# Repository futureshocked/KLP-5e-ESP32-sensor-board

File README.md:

View this project on [CADLAB.io](https://cadlab.io/project/28685). 

## Project Summary: Custom IoT PCB with ESP32-C3-02 and TP4056 Li-ion Charger

This project involves the design and development of a custom PCB for an IoT application powered by the ESP32-C3-02 SoC. The board includes integrated power management features using the TP4056 Li-ion battery charger IC, enabling efficient and safe charging of a single-cell Li-ion battery.

### Key Features

- **Microcontroller**: ESP32-C3-02 SoC for Wi-Fi and BLE connectivity.
- **Power Management**: TP4056 IC for single-cell Li-ion battery charging with thermal regulation.
- **Battery Protection**: Integrated under-voltage lockout and trickle charging.
- **Sensors and Modules**:
  - BME280 for temperature, humidity, and pressure sensing.
  - Ambient light and sound sensors.
  - Mini SD card reader for data storage.
  - Flash memory for additional storage.
- **Display**: I2C OLED for real-time data visualization.
- **Power Inputs**:
  - USB-C connector for charging and data transfer.
  - LiPo battery connector with onboard charging circuitry.
- **Indicators**: LED indicators for charge status (charging and full).

### Design Highlights

1. **Power Supply Integration**:
   - USB-C provides power for both charging and system operation.
   - TP4056 handles battery charging and protection.
   - Power supplied to the ESP32-C3-02 is regulated for stability.

2. **Modular Architecture**:
   - Supports various sensors and peripherals for IoT applications.
   - Expandable via additional I2C devices.

3. **Safe and Efficient Charging**:
   - Programmable charging current using an external resistor.
   - Automatic charge termination and battery protection.

4. **Compact and Reliable Layout**:
   - Optimized PCB traces for minimal power loss.
   - Thermal management for the TP4056 and other components.

### Applications

- IoT edge devices for environmental monitoring.
- Battery-powered data logging systems.
- Prototyping platform for ESP32-based projects.

### Repository Contents

- **Schematic and PCB Layout**: KiCad files for the board design.
- **Firmware**: Source code for the ESP32-C3-02 to interface with sensors and peripherals.
- **Documentation**:
  - Datasheets for the TP4056 and other components.
  - Assembly instructions.
  - Testing procedures.
- **License**: MIT License.

This repository is a complete resource for designing and building a robust IoT solution with integrated power management and ESP32 connectivity.

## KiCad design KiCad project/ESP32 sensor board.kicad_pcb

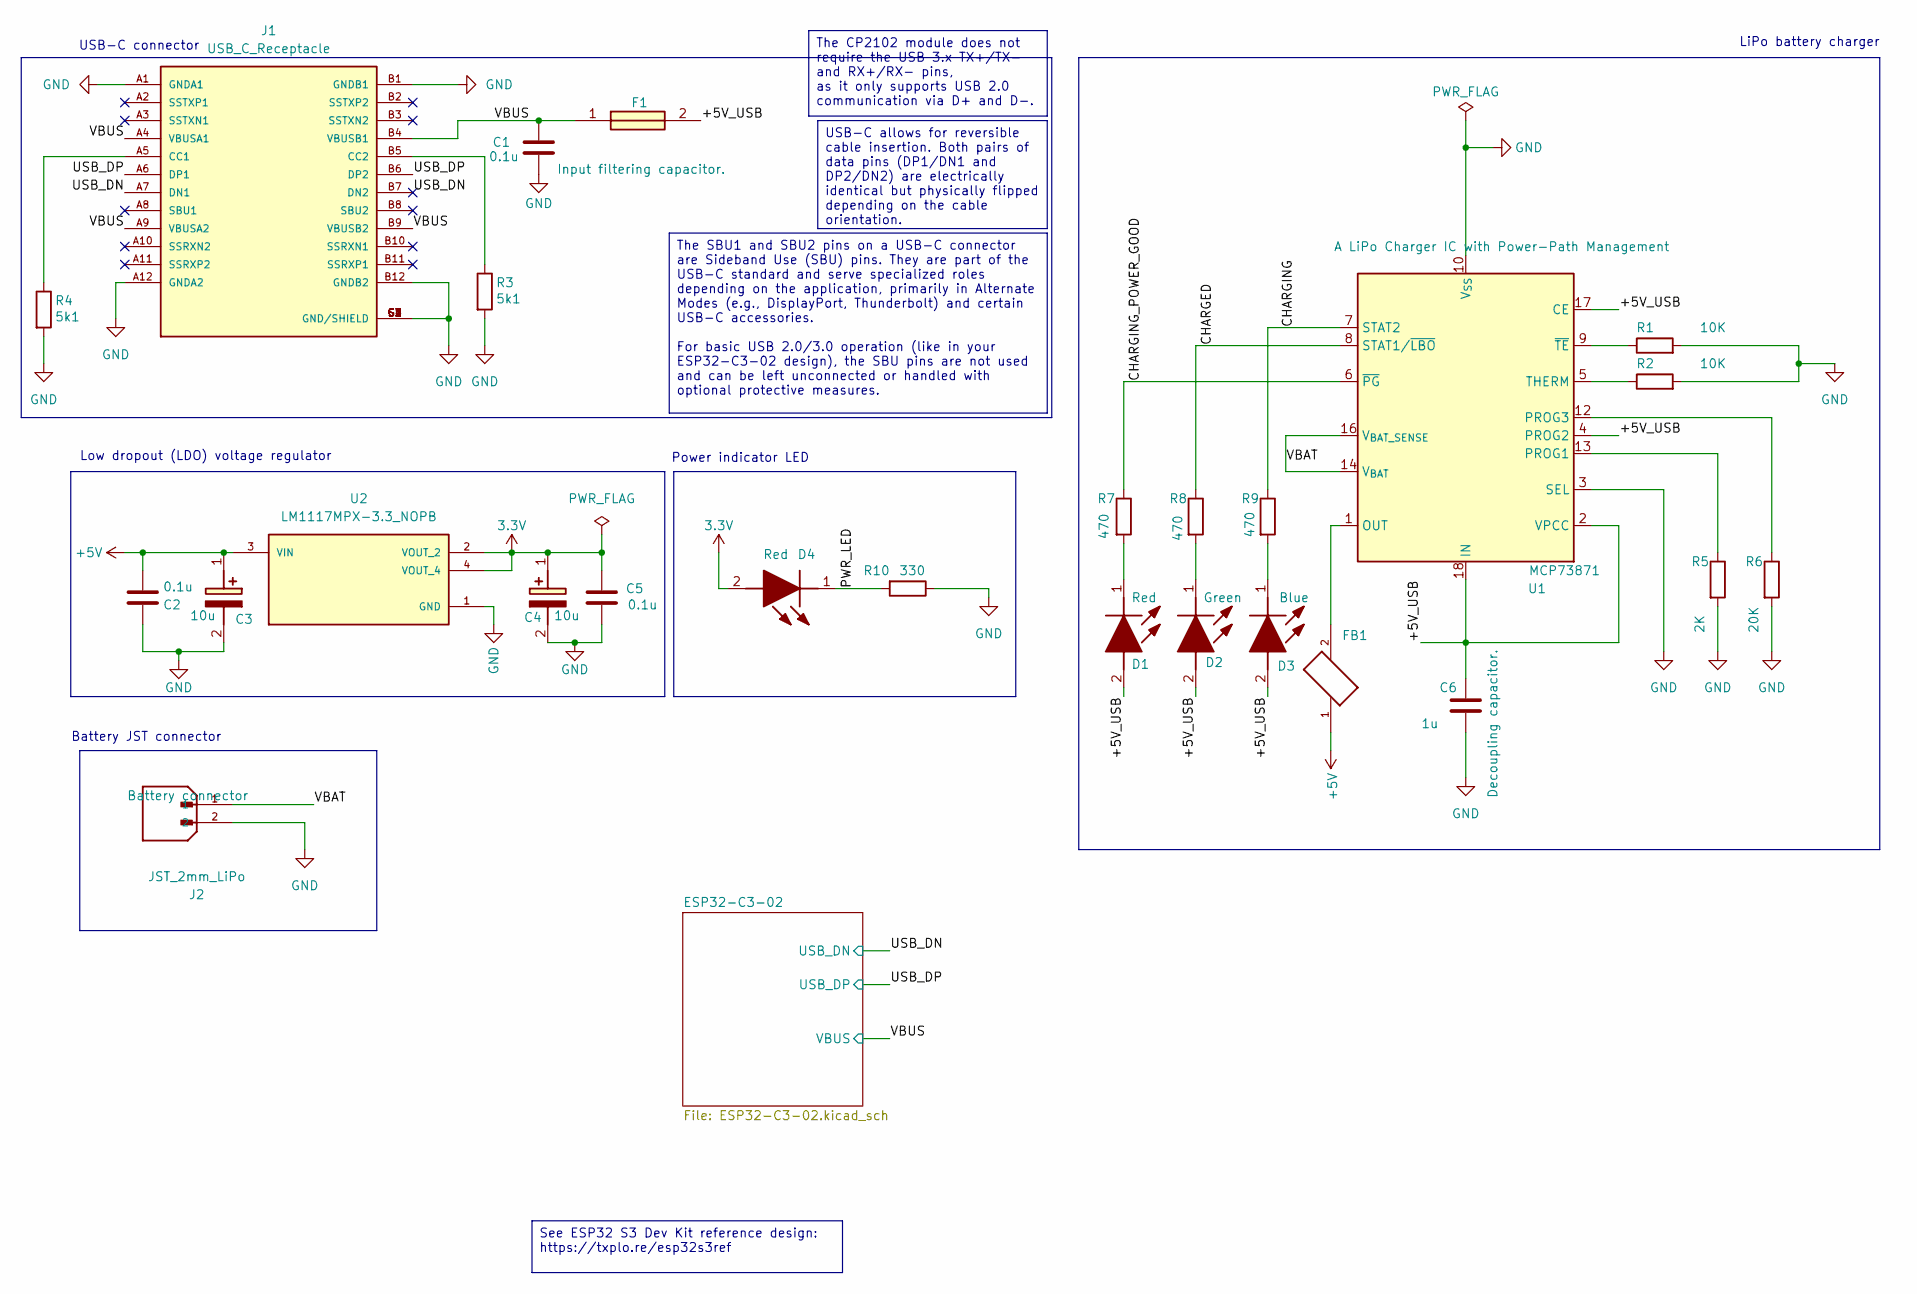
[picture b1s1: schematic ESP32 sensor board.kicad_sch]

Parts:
C1, C2, C5: 0.1u; C_0805_2012Metric; Voltage 1kV; Tolerance 100%
C3, C4: 10u; T491A; Voltage 1kV; Tolerance 100%; Manufacturer_Part_Number T491A106K010AT7280; Mouser Part Number 80-T491A106K107280
C6: 1u; C_0805_2012Metric; Voltage 1kV; Tolerance 100%
D1, D4: Red; LEDC2012X120N; Manufacturer_Part_Number LTST-C170KRKT; Mouser Part Number 859-LTST-C170KRKT
D2: Green; LEDC2012X120N; Manufacturer_Part_Number LTST-C170GKT; Mouser Part Number 859-LTST-C170GKT
D3: Blue; LEDC2012X120N; Manufacturer_Part_Number LTST-C170TBKT; Mouser Part Number 859-LTST-C170TBKT
F1: 0ZCH0110AF2E; FUSC3226X100N; Manufacturer_Part_Number 0ZCH0110AF2E
FB1: FBMJ2125HM330-T; BEADC2012X105N
J1: USB_C_Receptacle; BELFUSE_SS-52400-002; PARTREV A0
J2: JST_2mm_LiPo; JST_B2B-PH-SM4-TB; Manufacturer_Part_Number ?
R1, R2: 10K; R_0805_2012Metric
R3, R4: 5k1; R_0805_2012Metric
R5: 2K; R_0805_2012Metric
R6: 20K; R_0805_2012Metric
R7, R8, R9: 470; R_0805_2012Metric
R10: 330; R_0805_2012Metric
U1: MCP73871; QFN-20-1EP_4x4mm_P0.5mm_EP2.5x2.5mm; Manufacturer_Part_Number MCP73871-4CCI/ML
U2: LM1117MPX-3.3_NOPB; VREG_LM1117MPX-3.3; Mouser Part Number 926-LM1117MPX3.3NOPB

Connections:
3.3V: C4.1 (+), C5.1, D4.2 (A), U2.2 (VOUT_2), U2.4 (VOUT_4); also elsewhere on the board
+5V: C2.1, C3.1 (+), FB1.1, U2.3 (VIN)
/+5V_USB: C6.1, D1.2 (A), D2.2 (A), D3.2 (A), F1.2, U1.2 (VPCC), U1.4 (PROG2), U1.17 (CE), U1.18 (IN), U1.19 (IN)
/CHARGED: R8.1, U1.8 (STAT1/~LBO)
/CHARGING: R9.1, U1.7 (STAT2)
/CHARGING_POWER_GOOD: R7.1, U1.6 (~PG)
/PWR_LED: D4.1 (K), R10.2
/USB_DN: J1.A7 (DN1), J1.B7 (DN2); also elsewhere on the board
/USB_DP: J1.A6 (DP1), J1.B6 (DP2); also elsewhere on the board
/VBAT: J2.1, U1.14 (V_{BAT}), U1.15 (V_{BAT}), U1.16 (V_{BAT_SENSE})
/VBUS: C1.1, F1.1, J1.A4 (VBUSA1), J1.A9 (VBUSA2), J1.B4 (VBUSB1), J1.B9 (VBUSB2); also elsewhere on the board
GND: C1.2, C2.2, C3.2 (-), C4.2 (-), C5.2, C6.2, J1.A1 (GNDA1), J1.A12 (GNDA2), J1.B1 (GNDB1), J1.B12 (GNDB2), J1.G1 (GND/SHIELD), J1.G2 (GND/SHIELD), J1.G3 (GND/SHIELD), J1.G4 (GND/SHIELD), J1.S1 (GND/SHIELD), J1.S2 (GND/SHIELD), J1.S3 (GND/SHIELD), J1.S4 (GND/SHIELD), J2.2, R1.2, R2.2, R3.2, R4.2, R5.2, R6.2, R10.1, U1.3 (SEL), U1.10 (V_{SS}), U1.11 (V_{SS}), U1.21 (V_{SS}), U2.1 (GND); also elsewhere on the board
unnamed: D1.1 (K), R7.2
unnamed: D2.1 (K), R8.2
unnamed: D3.1 (K), R9.2
unnamed: FB1.2, U1.1 (OUT), U1.20 (OUT)
unnamed: J1.A5 (CC1), R4.1
unnamed: J1.B5 (CC2), R3.1
unnamed: R5.1, U1.13 (PROG1)
unnamed: R6.1, U1.12 (PROG3)
unnamed: R2.1, U1.5 (THERM)
unnamed: R1.1, U1.9 (~TE)

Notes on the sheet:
USB-C connector
LiPo battery charger
Power indicator LED
Low dropout (LDO) voltage regulator
Battery JST connector
The CP2102 module does not require the USB 3.x TX+/TX- and RX+/RX- pins, as it only supports USB 2.0 communication via D+ and D-.
See ESP32 S3 Dev Kit reference design: https://txplo.re/esp32s3ref
The SBU1 and SBU2 pins on a USB-C connector are Sideband Use (SBU) pins. They are part of the USB-C standard and serve specialized roles depending on the application, primarily in Alternate Modes (e.g., DisplayPort, Thunderbolt) and certain USB-C accessories. For basic USB 2.0/3.0 operation (like i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
USB-C allows for reversible cable insertion. Both pairs of data pins (DP1/DN1 and DP2/DN2) are electrically identical but physically flipped depending on the cable orientation.

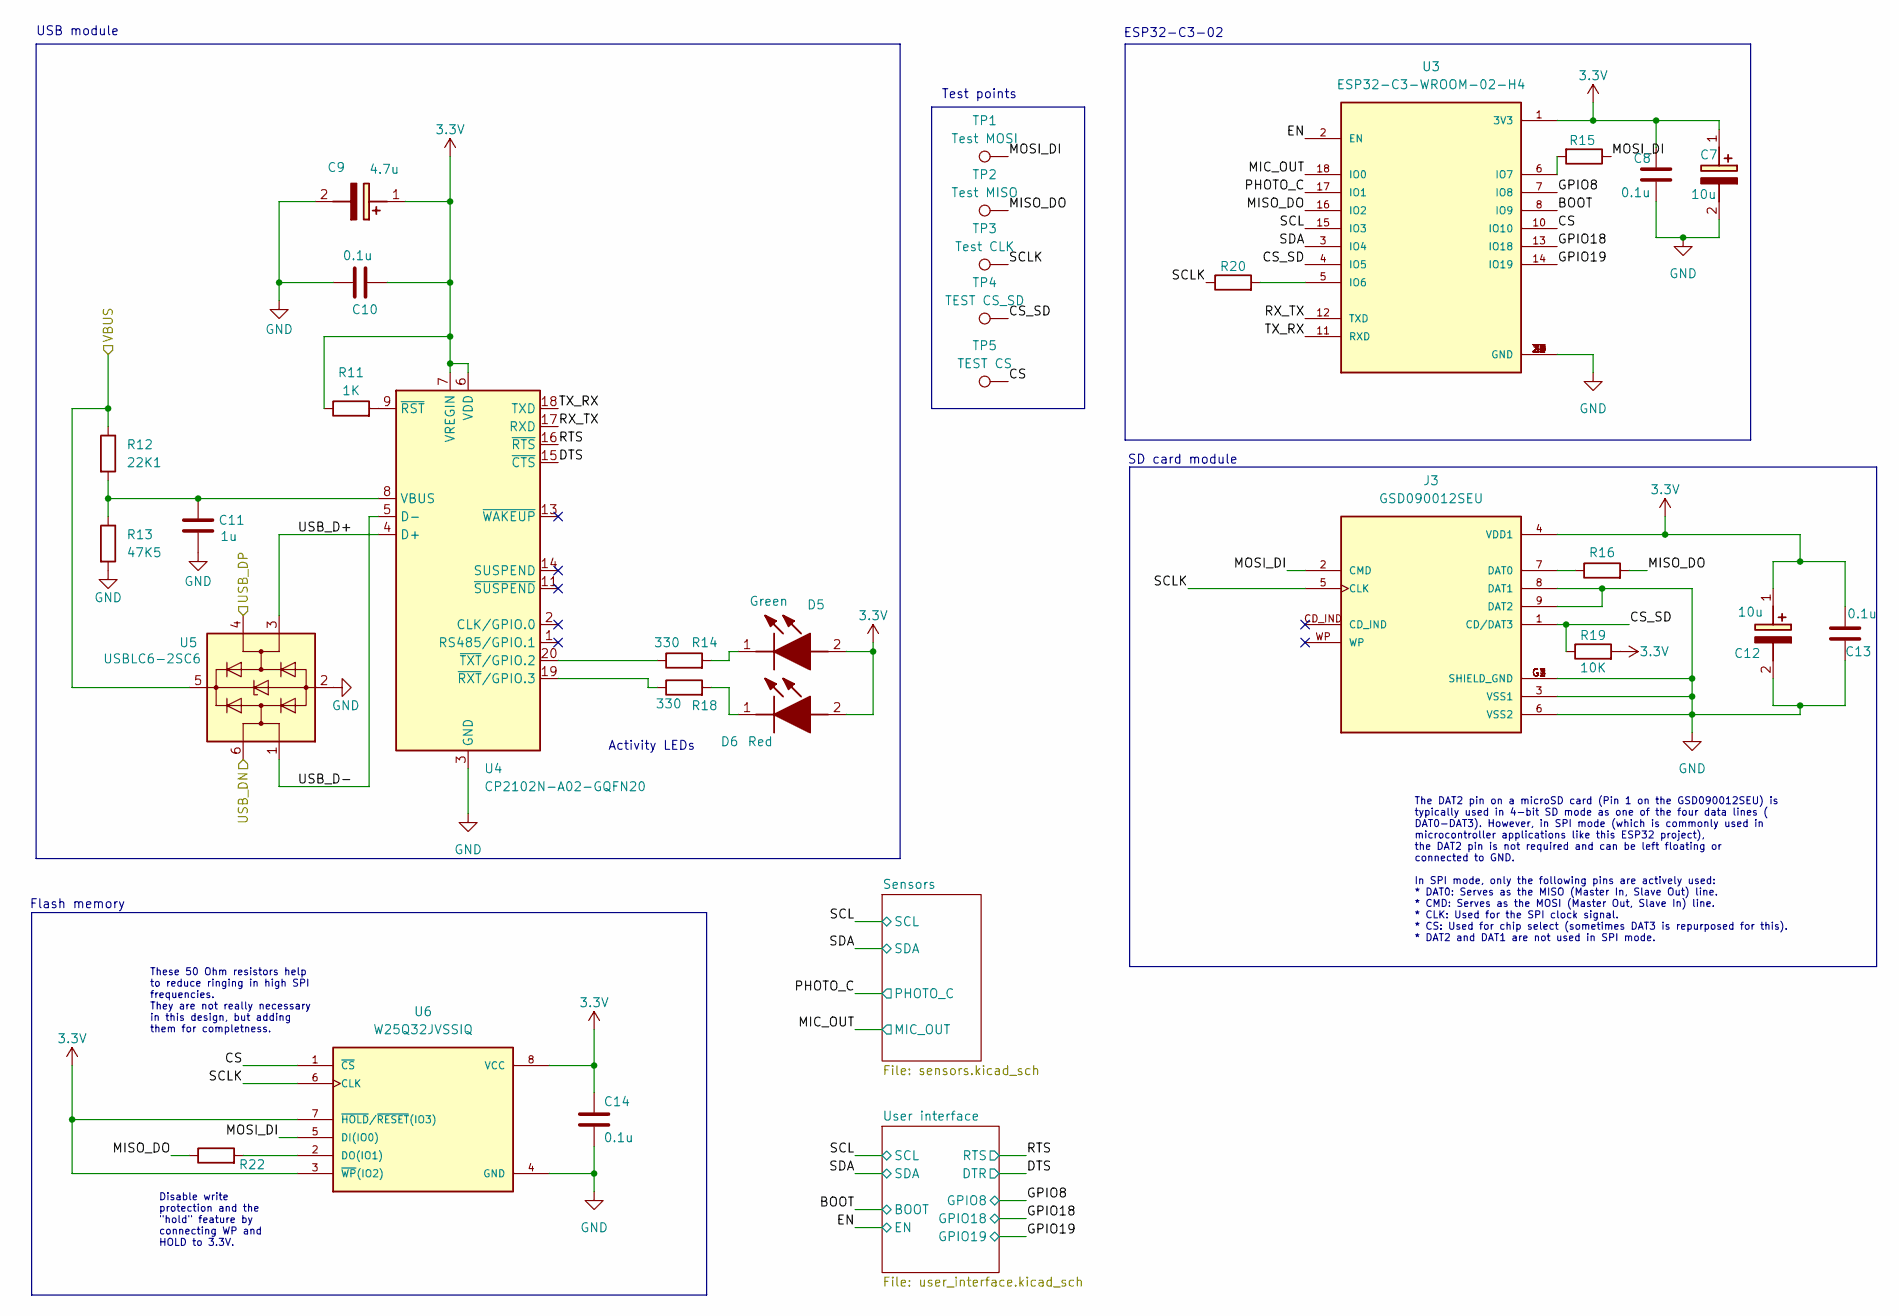
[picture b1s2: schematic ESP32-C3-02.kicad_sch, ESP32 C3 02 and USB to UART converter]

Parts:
C7, C12: 10u; T491A; Voltage 1kV; Tolerance 100%; Manufacturer_Part_Number T491A106K010AT7280; Mouser Part Number 80-T491A106K107280
C8, C10, C13, C14: 0.1u; C_0805_2012Metric; Voltage 1kV; Tolerance 100%
C9: 4.7u; T491A; Voltage 1kV; Tolerance 100%; Manufacturer_Part_Number T491A106K010AT7280; Mouser Part Number 80-T491A106K107280
C11: 1u; C_0805_2012Metric; Voltage 1kV; Tolerance 100%
D5: Green; LEDC2012X120N; Manufacturer_Part_Number LTST-C170GKT; Mouser Part Number 859-LTST-C170GKT
D6: Red; LEDC2012X120N; Manufacturer_Part_Number LTST-C170KRKT; Mouser Part Number 859-LTST-C170KRKT
J3: GSD090012SEU; AMPHENOL_GSD090012SEU; PARTREV E
R11: 1K; R_0805_2012Metric
R12: 22K1; R_0805_2012Metric
R13: 47K5; R_0805_2012Metric
R14, R18: 330; R_0805_2012Metric
R15, R16, R20, R22: 50; R_0805_2012Metric
R19: 10K; R_0805_2012Metric
TP1: Test MOSI; TestPoint_Pad_D1.0mm
TP2: Test MISO; TestPoint_Pad_D1.0mm
TP3: Test CLK; TestPoint_Pad_D1.0mm
TP4: TEST CS_SD; TestPoint_Pad_D1.0mm
TP5: TEST CS; TestPoint_Pad_D1.0mm
U3: ESP32-C3-WROOM-02-H4; MODULE_ESP32-C3-WROOM-02-H4; Manufacturer_Part_Number ESP32-C3-WROOM-02-H4
U4: CP2102N-A02-GQFN20; SiliconLabs_QFN-20-1EP_3x3mm_P0.5mm_EP1.8x1.8mm; Manufacturer_Part_Number CP2102N-A02-GQFN20
U5: USBLC6-2SC6; SOT-23-6; Manufacturer_Part_Number USBLC6-2SC6; Mouser Part Number 511-USBLC6-2SC6
U6: W25Q32JVSSIQ; SOIC127P790X216-8N; M_PART_NUMBER W25QXX

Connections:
3.3V: C7.1 (+), C8.1, C9.1 (+), C10.1, C12.1 (+), C13.2, C14.1, D5.2 (A), D6.2 (A), J3.4 (VDD1), R11.1, R19.2, U3.1 (3V3), U4.6 (VDD), U4.7 (VREGIN), U6.3 (~WP(IO2)), U6.7 (~HOLD/~RESET(IO3)), U6.8 (VCC); also elsewhere on the board
/ESP32-C3-02/BOOT: U3.8 (IO9); also elsewhere on the board
/ESP32-C3-02/CS: TP5.1, U3.10 (IO10), U6.1 (~CS)
/ESP32-C3-02/CS_SD: J3.1 (CD/DAT3), R19.1, TP4.1, U3.4 (IO5)
/ESP32-C3-02/DTS: U4.15 (~CTS); also elsewhere on the board
/ESP32-C3-02/EN: U3.2 (EN); also elsewhere on the board
/ESP32-C3-02/GPIO8: U3.7 (IO8); also elsewhere on the board
/ESP32-C3-02/GPIO18: U3.13 (IO18); also elsewhere on the board
/ESP32-C3-02/GPIO19: U3.14 (IO19); also elsewhere on the board
/ESP32-C3-02/MIC_OUT: U3.18 (IO0); also elsewhere on the board
/ESP32-C3-02/MISO_DO: R16.2, R22.1, TP2.1, U3.16 (IO2)
/ESP32-C3-02/MOSI_DI: J3.2 (CMD), R15.1, TP1.1, U6.5 (DI(IO0))
/ESP32-C3-02/PHOTO_C: U3.17 (IO1); also elsewhere on the board
/ESP32-C3-02/RTS: U4.16 (~RTS); also elsewhere on the board
/ESP32-C3-02/RX_TX: U3.12 (TXD), U4.17 (RXD)
/ESP32-C3-02/SCL: U3.15 (IO3); also elsewhere on the board
/ESP32-C3-02/SCLK: J3.5 (CLK), R20.1, TP3.1, U6.6 (CLK)
/ESP32-C3-02/SDA: U3.3 (IO4); also elsewhere on the board
/ESP32-C3-02/TX_RX: U3.11 (RXD), U4.18 (TXD)
/ESP32-C3-02/USB_D+: U4.4 (D+), U5.3 (I/O2)
/ESP32-C3-02/USB_D-: U4.5 (D-), U5.1 (I/O1)
/USB_DN: U5.6 (I/O1); also elsewhere on the board
/USB_DP: U5.4 (I/O2); also elsewhere on the board
/VBUS: R12.1, U5.5 (VBUS); also elsewhere on the board
GND: C7.2 (-), C8.2, C9.2 (-), C10.2, C11.2, C12.2 (-), C13.1, C14.2, J3.3 (VSS1), J3.6 (VSS2), J3.8 (DAT1), J3.9 (DAT2), J3.G1 (SHIELD_GND), J3.G2 (SHIELD_GND), J3.G3 (SHIELD_GND), J3.G4 (SHIELD_GND), R13.2, U3.9 (GND), U3.19 (GND), U3.20 (GND), U3.21 (GND), U3.22 (GND), U3.23 (GND), U3.24 (GND), U3.25 (GND), U3.26 (GND), U3.27 (GND), U3.28 (GND), U3.29 (GND), U3.30 (GND), U3.31 (GND), U3.32 (GND), U3.33 (GND), U3.34 (GND), U3.35 (GND), U3.36 (GND), U3.37 (GND), U3.38 (GND), U3.39 (GND), U4.3 (GND), U4.12 (GND), U4.21 (GND), U5.2 (GND), U6.4 (GND); also elsewhere on the board
unnamed: D5.1 (K), R14.2
unnamed: D6.1 (K), R18.2
unnamed: J3.7 (DAT0), R16.1
unnamed: R20.2, U3.5 (IO6)
unnamed: R15.2, U3.6 (IO7)
unnamed: C11.1, R12.2, R13.1, U4.8 (VBUS)
unnamed: R11.2, U4.9 (~RST)
unnamed: R18.1, U4.19 (~RXT/GPIO.3)
unnamed: R14.1, U4.20 (~TXT/GPIO.2)
unnamed: R22.2, U6.2 (DO(IO1))

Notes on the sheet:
SD card module
Activity LEDs
Flash memory
USB module
Test points
ESP32-C3-02
Disable write protection and the "hold" feature by connecting WP and HOLD to 3.3V.
The DAT2 pin on a microSD card (Pin 1 on the GSD090012SEU) is typically used in 4-bit SD mode as one of the four data lines ( DAT0-DAT3). However, in SPI mode (which is commonly used in microcontroller applications like this ESP32 project), the DAT2 pin is not required and can be left floating or c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
These 50 Ohm resistors help to reduce ringing in high SPI frequencies. They are not really necessary in this design, but adding them for completness.

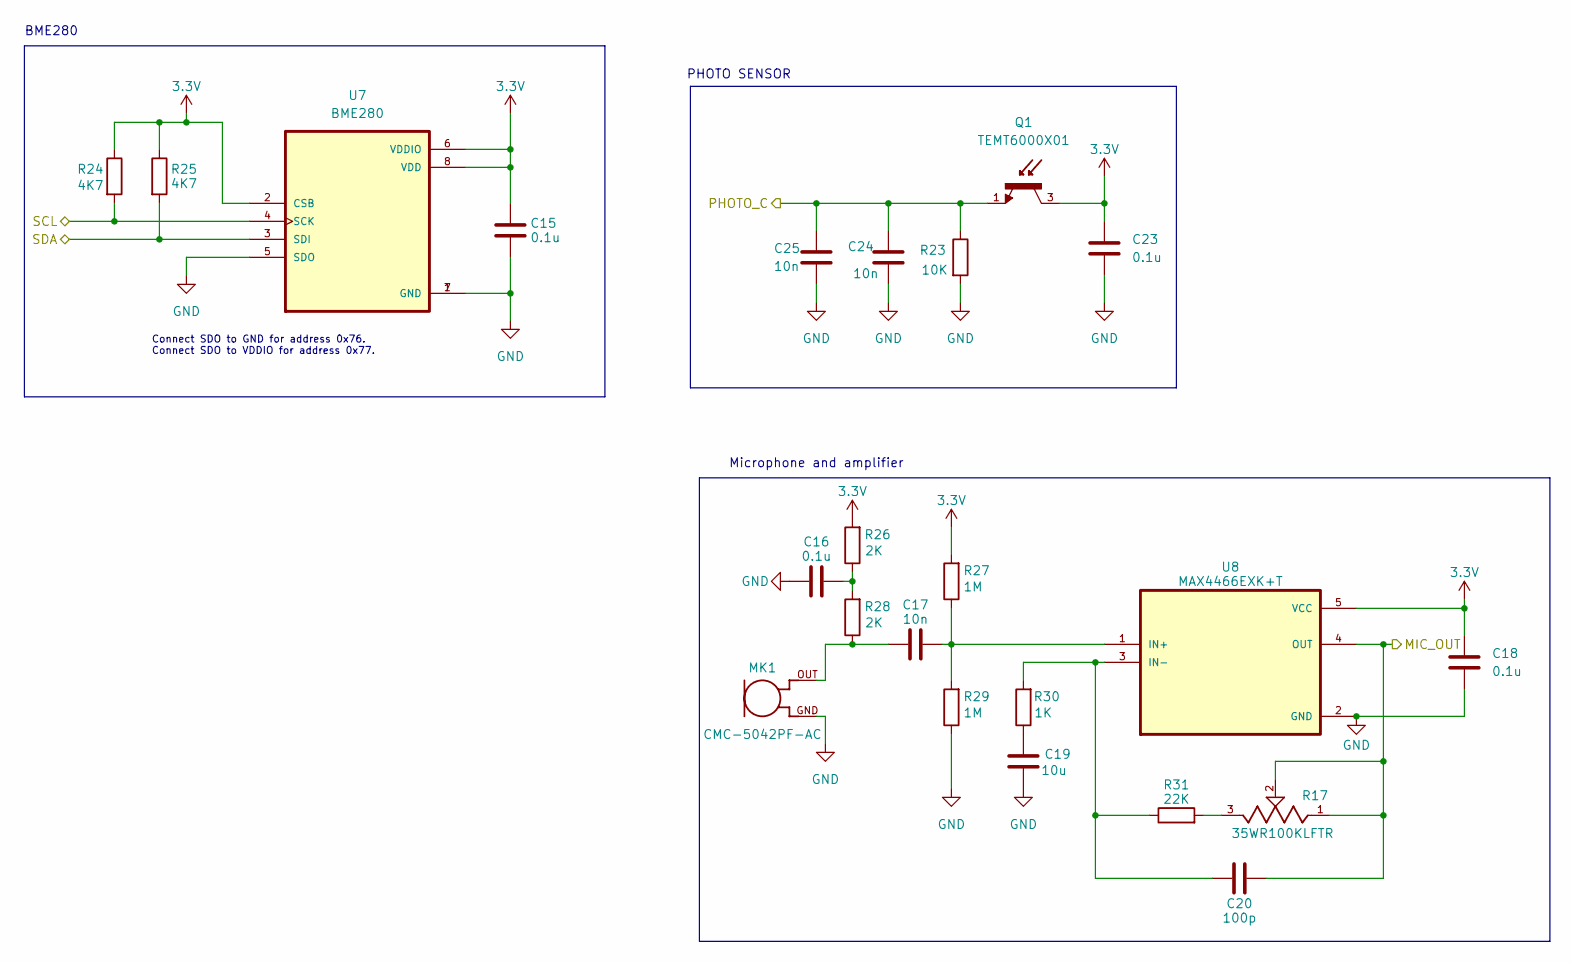
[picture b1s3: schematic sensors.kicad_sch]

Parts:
C15: 0.1u; C_0805_2012Metric; Voltage 1kV; Tolerance 100%
C16, C18, C23: 0.1u; C_0805_2012Metric
C17, C24, C25: 10n; C_0805_2012Metric
C19: 10u; C_0805_2012Metric
C20: 100p; C_0805_2012Metric
MK1: CMC-5042PF-AC; CUI_CMC-5042PF-AC; Manufacturer_Part_Number CMC-5042PF-AC
Q1: TEMT6000X01; TRANS_TEMT6000X01; PARTREV 1.9
R17: 35WR100KLFTR; TRIM_35WR100KLFTR; PARTREV D
R23: 10K; R_0805_2012Metric
R24, R25: 4K7; R_0805_2012Metric
R26, R28: 2K; R_0805_2012Metric
R27, R29: 1M; R_0805_2012Metric
R30: 1K; R_0805_2012Metric
R31: 22K; R_0805_2012Metric
U7: BME280; PSON65P250X250X100-8N; Manufacturer_Part_Number BME280
U8: MAX4466EXK+T; SOT65P210X110-5N; Manufacturer_Part_Number MAX4466EXK+T

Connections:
3.3V: C15.2, C18.1, C23.1, Q1.3, R24.1, R25.1, R26.2, R27.2, U7.2 (CSB), U7.6 (VDDIO), U7.8 (VDD), U8.5 (VCC); also elsewhere on the board
/ESP32-C3-02/MIC_OUT: C20.2, R17.1, R17.2, U8.4 (OUT); also elsewhere on the board
/ESP32-C3-02/PHOTO_C: C24.1, C25.1, Q1.1, R23.1; also elsewhere on the board
/ESP32-C3-02/SCL: R24.2, U7.4 (SCK); also elsewhere on the board
/ESP32-C3-02/SDA: R25.2, U7.3 (SDI); also elsewhere on the board
GND: C15.1, C16.2, C18.2, C19.1, C23.2, C24.2, C25.2, MK1.GND, R23.2, R29.1, U7.1 (GND), U7.5 (SDO), U7.7 (GND), U8.2 (GND); also elsewhere on the board
unnamed: C16.1, R26.1, R28.2
unnamed: C17.2, MK1.OUT, R28.1
unnamed: C19.2, R30.1
unnamed: R17.3, R31.2
unnamed: C17.1, R27.1, R29.2, U8.1 (IN+)
unnamed: C20.1, R30.2, R31.1, U8.3 (IN-)

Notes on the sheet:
PHOTO SENSOR
Microphone and amplifier
BME280
Connect SDO to GND for address 0x76. Connect SDO to VDDIO for address 0x77.

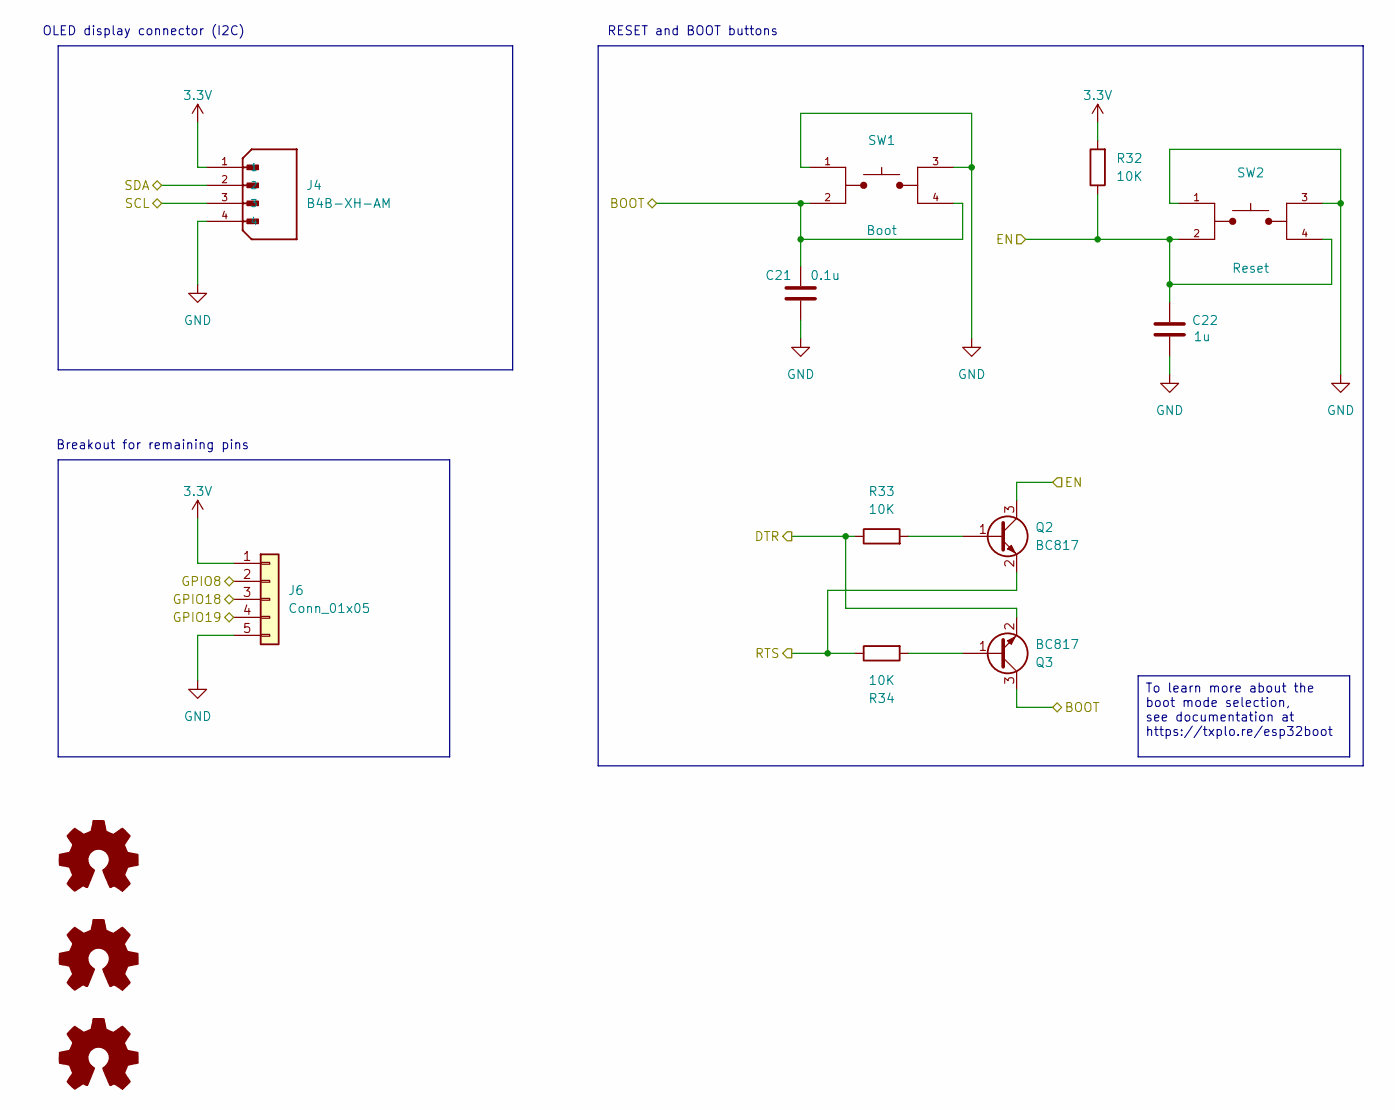
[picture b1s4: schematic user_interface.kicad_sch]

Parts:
C21: 0.1u; C_0805_2012Metric; Voltage 1kV; Tolerance 100%
C22: 1u; C_0805_2012Metric; Voltage 1kV; Tolerance 100%
J4: B4B-XH-AM; JST_B4B-XH-AM__LF__SN_; PARTREV N/A
J6: Conn_01x05; PinHeader_1x05_P2.54mm_Vertical
Q2, Q3: BC817; SOT-23; Manufacturer_Part_Number BC817
R32, R33, R34: 10K; R_0805_2012Metric
SW1, SW2: 1101NE; SW_TL3305AF260QG; Mfg Part# 8-004 SMD Button 8x3.6mm Height=2.5mm

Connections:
3.3V: J4.1, J6.1, R32.2; also elsewhere on the board
/ESP32-C3-02/BOOT: C21.1, Q3.3 (C), SW1.2, SW1.4; also elsewhere on the board
/ESP32-C3-02/DTS: Q3.2 (E), R33.1; also elsewhere on the board
/ESP32-C3-02/EN: C22.1, Q2.3 (C), R32.1, SW2.2, SW2.4; also elsewhere on the board
/ESP32-C3-02/GPIO8: J6.2; also elsewhere on the board
/ESP32-C3-02/GPIO18: J6.3; also elsewhere on the board
/ESP32-C3-02/GPIO19: J6.4; also elsewhere on the board
/ESP32-C3-02/RTS: Q2.2 (E), R34.1; also elsewhere on the board
/ESP32-C3-02/SCL: J4.3; also elsewhere on the board
/ESP32-C3-02/SDA: J4.2; also elsewhere on the board
GND: C21.2, C22.2, J4.4, J6.5, SW1.1, SW1.3, SW2.1, SW2.3; also elsewhere on the board
unnamed: Q2.1 (B), R33.2
unnamed: Q3.1 (B), R34.2

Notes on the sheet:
OLED display connector (I2C)
RESET and BOOT buttons
Breakout for remaining pins
To learn more about the boot mode selection, see documentation at https://txplo.re/esp32boot

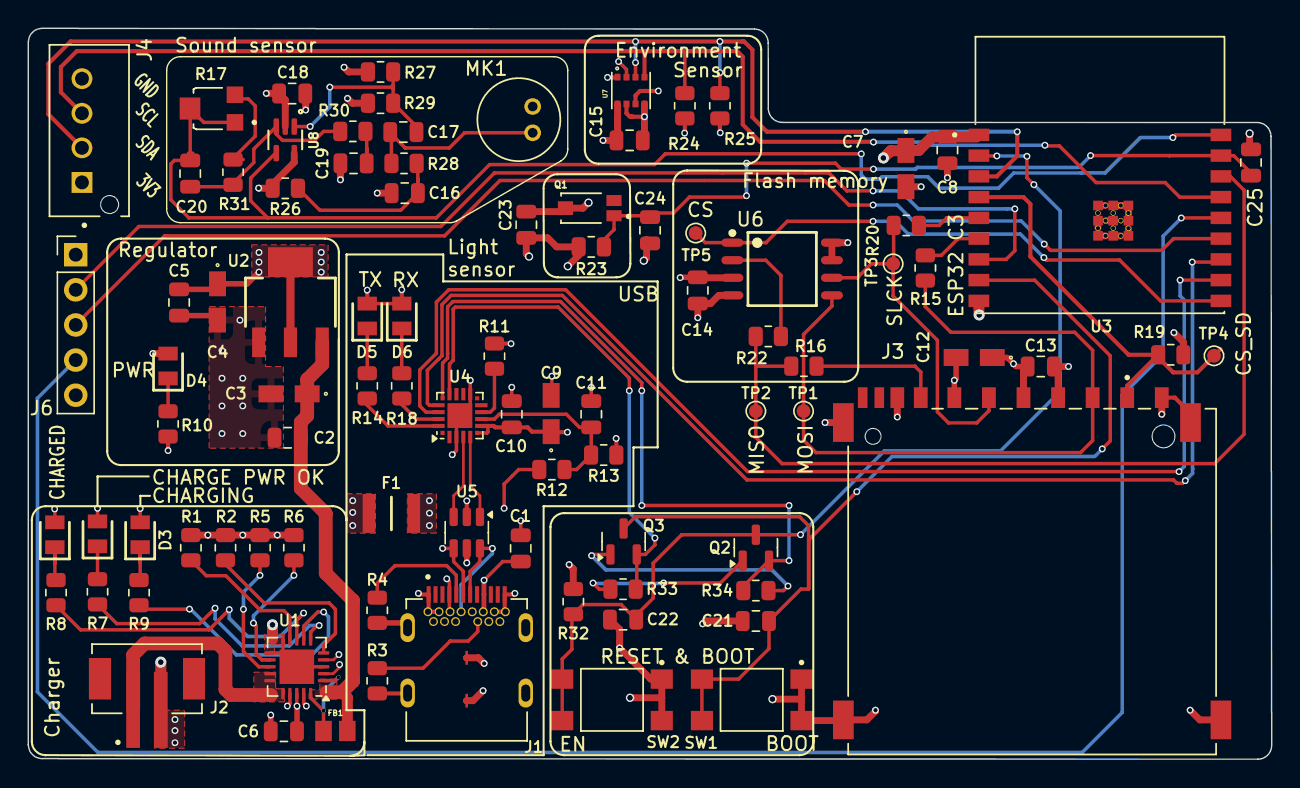
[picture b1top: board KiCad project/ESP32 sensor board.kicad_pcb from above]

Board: 4 copper layers, 89.9 x 52.8 mm, 90 parts (0 on the bottom side), 60 nets.

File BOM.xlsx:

DESIGNATOR | QTY | VALUE | MANUF. PART No | MANUFACTURER | PACKAGE | DESCRIPTION
> C1, C2, C5, C8, C10, C13-C16, C18, C20, C21 | 12 | 0.1u | C0805C104K4RAC | KEMET | 805 | Multilayer Ceramic Capacitors MLCC - SMD/SMT 16V 0.1uF X7R 0805 10%
> C3, C4, C7, C12 | 4 | 10u | T491A106K010AT7280 | KEMET | 1206 | T491, Tantalum, MnO2 Tantalum, Commercial Grade, 10 uF, 10%, 10 VDC, 125C, -55C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
> C6, C11, C19, C22 | 4 | 1u | C0805C105K4RACTU | KEMET | 805 | Multilayer Ceramic Capacitors MLCC - SMD/SMT 16V 1uF X7R 0805 10%
C9 | 1 | 4.7u | T491A475K010AT7280 | KEMET | 1206 | T491, Tantalum, MnO2 Tantalum, Commercial Grade, 4.7 uF, 10%, 10 VDC, 125C, -55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
C17 | 1 | 10n | C0805C103M4RACTU | KEMET | 805 | Multilayer Ceramic Capacitors MLCC - SMD/SMT 16V 0.01uF X7R 0805 20%
> D1, D4, D6 | 3 | RED | LTST-C170KRKT | Lite-On | 805 | Standard LEDs - SMD Red Clear 631nm
> D2, D5 | 2 | GREEN | LTST-C170GKT | Lite-On | 805 | LED,SMD,0805,Green,6mcd,130deg Lite-On LTST-C170GKT, CHIPLED 0805 Series Green 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
D3 | 1 | BLUE | LTST-C170TBKT | Lite-On | 805 | LED,SMD,0805,Blue,28mcd,130deg
F1 | 1 | 0ZCH0110AF2E | 0ZCH0110AF2E | Belfuse | 1210 | 1210 SMT PPTC | 1.10 Ih | 16V
J1 | 1 | USB_C_Receptacle | Footprints:BELFUSE_SS-52400-002 | BELFUSE Stewart Connector | SS-52400-003 for standard 1.6 mm PCB thickness | USB 2.0-only Type-C Receptacle connector. See https://www.snapeda.com/parts/SS-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
J2 | 1 | JST_2mm_LiPo | JST_B2B-PH-SM4-TB | JST |  | 2 Pin 2mm JST Battery Connector
J3 | 1 | GSD090012SEU | GSD090012SEU | Amphenol |  | Memory Card Connectors SD CARD CONNECTOR 9 POS, SMT
> J4, J5 | 2 | B4B-XH-AM | B4B-XH-AM | JST |  | Connector header vertical 4pos 2.5mm
J6 | 1 | Conn_01x05 |  |  |  | Header 1X5, 2.54mm
MK1 | 1 | CMC-5042PF-AC | CMC-5042PF-AC | CUI INC |  | Microphone
Q1 | 1 | TEMT6000X01 | TEMT6000X01 | VISHAY | 4 mm x 2 mm x 1.05 mm | Ambient Light Sensors Ambient Light Sensor AEC-Q101 Qualified
> Q2, Q3 | 2 | BC817 | BC817 |  | SOT-23 | 0.8A Ic, 45V Vce, NPN Transistor, SOT-23
> R1, R2, R19, R23, R30, R32-R34 | 8 | 10K |  |  | 805 | SMD resistor, 0805, 125mW, 1%
> R3, R4 | 2 | 5k1 |  |  | 0805 | SMD resistor, 0805, 125mW, 1%
> R5, R26, R28 | 3 | 2K |  |  | 0805 | SMD resistor, 0805, 125mW, 1%
R6 | 1 | 20K |  |  | 0805 | SMD resistor, 0805, 125mW, 1%
> R7-R9 | 3 | 470 |  |  | 0805 | SMD resistor, 0805, 125mW, 1%
> R10, R14, R18 | 3 | 330 |  |  | 0805 | SMD resistor, 0805, 125mW, 1%
R11 | 1 | 1K |  |  | 0805 | SMD resistor, 0805, 125mW, 1%
R12 | 1 | 22K1 |  |  | 0805 | SMD resistor, 0805, 125mW, 1%
R13 | 1 | 47K5 |  |  | 0805 | SMD resistor, 0805, 125mW, 1%
> R15-R17, R20-R22 | 6 | 50 |  |  | 0805 | SMD resistor, 0805, 125mW, 1%
> R24, R25 | 2 | 4K7 |  |  | 0805 | SMD resistor, 0805, 125mW, 1%
> R27, R29 | 2 | 1M |  |  | 0805 | SMD resistor, 0805, 125mW, 1%
R31 | 1 | 100K |  |  | 0805 | SMD resistor, 0805, 125mW, 1%
> SW1, SW2 | 2 | 1101NE | USLPT2819 Family | TE Connectivity | USLPT2819 MSLPT (Mini size) | SMD_6x3.5mm_h2.5mm. Please see https://www.snapeda.com/parts/USLPT2819DT2TR/TE%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
U1 | 1 | MCP73871 | MCP73871-4CCI/ML | Microchip | QFN50P400X400X100-21N | Single cell, Li-Ion/Li-Po charge management controller. See https://www.snapeda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
U2 | 1 | LM1117MPX-3.3_NOPB | LM1117MPX-33NOPB | On Semiconductor | SOT−223 CASE 318H | See https://www.snapeda.com/parts/LM1117MPX-33NOPB/ON%20Semicond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
U3 | 1 | ESP32-C3-WROOM-02-H4 | ESP32-C3-WROOM-02-H4 | Espressif |  | Multiprotocol Modules SMD module, ESP32-C3, 4MB SPI flash, PCB antenna
U4 | 1 | CP2102N-A02-GQFN20 | CP2102N-A02-GQFN20 | Silicon Laboratories | QFN20 | USB to UART Bridge
U5 | 1 | USBLC6-2SC6 | USBLC6-2SC6 | STMicroelectronics | SOT-23-6 | ESD Suppressors / TVS Diodes ESD Protection Low Cap
U6 | 1 | W25Q32JVSSIQ | W25Q32JVSSIQ | Winbond | SOIC-8 | NOR Flash spiFlash, 32M-bit, 4Kb Uniform Sector
U7 | 1 | BME280 | BME280 | Bosch | LGA-8 | Air Quality Sensor MEMS humidity, pressure and temperature sensor
U8 | 1 | MAX4466EXK+T | MAX4466EXK+T | Analog Devices Inc. | SC-70-5 | Microphone Preamplifier

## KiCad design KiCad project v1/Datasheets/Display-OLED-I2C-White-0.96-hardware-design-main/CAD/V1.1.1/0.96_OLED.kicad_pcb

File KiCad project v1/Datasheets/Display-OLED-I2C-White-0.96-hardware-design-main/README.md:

# Display OLED I2C White 0.96" SSD1306 Hardware design

## About the product

|  |
| :----------------------------------------------------------: |
|      [Buy Display OLED I2C White 0.96" SSD1306](https://www.solde.red/333099)      |

Looking to add visuals to your Arduino projects? The I2C OLED breakout board is perfect for that. Because of its high contrast, you will be in awe of its crispness! The display is made from hundreds of LEDs, each representing one pixel in a 128x64 grid. Thus, it doesn't need any backlight, and it needs less power than the classic LCD screens. That’s 8192 pixels all individually lit at your fingertips!

The design is 5V ready with an onboard regulator, so is compatible with any 3.3V board. The breakout board uses only about 20 mA, depending on active pixels. It is easy to control over the I2C interface. It is even easier to connect with the easyC system - no soldering required!

## Repository contents

All Soldered Electronics hardware designed in KiCAD, and repositories are organized in the following way:

- CAD folder - contains KiCAD files (Schematics, Board, Panel Board), sorted by version. Change log lists all changes between versions.
- OUTPUTS - contains useful files, such as Bill of Materials (BOM), PDF of schematics, 3D .step file of the board and gerber files, sorted by version. 
- OUTPUTS -> Compliance - Certificates and useful legal stuff. 

## Want to contribute?

Please feel free to submit a pull request if you have any contributions. We encourage you to submit an issue or pull request if you find a bug. 

## About Soldered

At Soldered, we design and manufacture a wide selection of electronic products to help you turn your ideas into acts and bring you one step closer to your final project. Our products are intented for makers and crafted in-house by our experienced team in Osijek, Croatia. We believe that sharing is a crucial element for improvement and innovation, and we work hard to stay connected with all our makers regardless of their skill or experience level. Therefore, all our products are open-source. Finally, we always have your back. If you face any problem concerning either your shopping experience or your electronics project, our team will help you deal with it, offering efficient customer service and cost-free technical support anytime. Some of those might be useful for you:

- [Web Store](https://www.soldered.com/shop)
- [Tutorials & Projects](https://soldered.com/learn)
- [Community & Technical support](https://soldered.com/community)

## License info

All Soldered open-source hardware (OSH) is under The TAPR Open Hardware License. Read more in the LICENSE file. 

No warranty - all designs in this repository are distributed in the hope that they will be useful, but without any warranty. They are provided "AS IS", therefore without warranty of any kind, either expressed or implied. The entire quality and performance of what you do with the contents of this repository are your responsibility. In no event, Soldered Electronics will be liable for your damages, losses, including any general, special, incidental or consequential damage arising out of the use or inability to use the contents of this repository. 

## Have fun! 
And thank you from your fellow makers at Soldered Electronics.

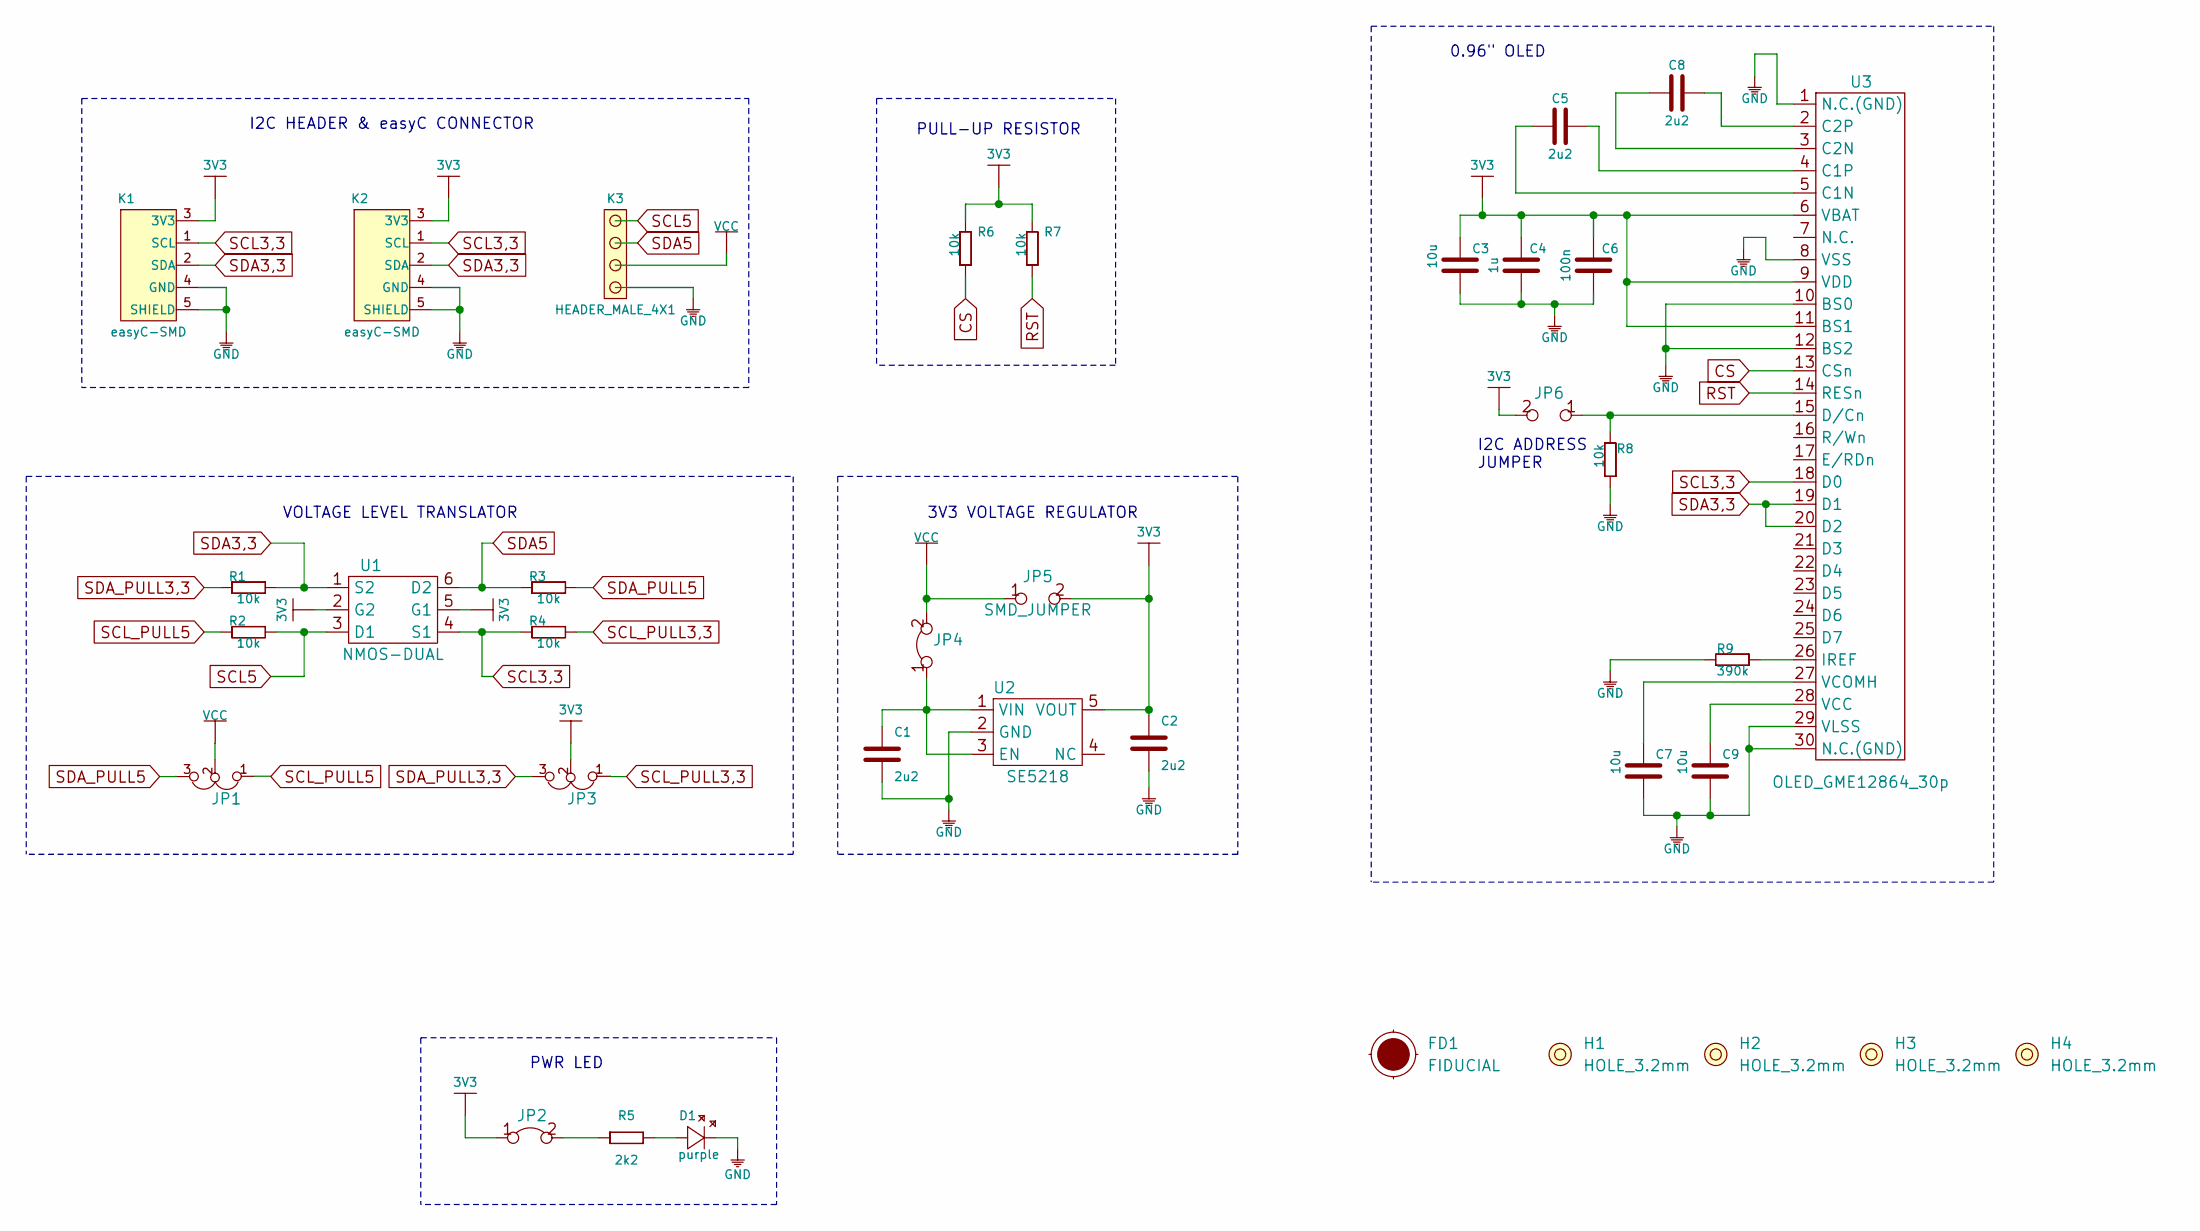
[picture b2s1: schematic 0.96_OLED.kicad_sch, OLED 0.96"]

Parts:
C1, C2, C5, C8: 2u2; 0603C
C3, C7, C9: 10u; 1206C
C4: 1u; 0603C
C6: 100n; 0603C
D1: purple; 0402LED
FD1: FIDUCIAL; FIDUCIAL_23
H1, H2, H3, H4: HOLE_3.2mm
JP1, JP3: SMD_JUMPER_3_PAD_TRACE
JP2, JP4: SMD-JUMPER-CONNECTED_TRACE_SLODERMASK
JP5, JP6: SMD_JUMPER
K1, K2: easyC-SMD; easyC-connector
K3: HEADER_MALE_4X1
R1, R2, R3, R4, R6, R7, R8: 10k; 0603R
R5: 2k2; 0402R
R9: 390k; 0603R
U1: NMOS-DUAL; SOT-363
U2: SE5218; SOT-23-5
U3: OLED_GME12864_30p; OLED_GME128x64_30p

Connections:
3V3: C2.2, C3.1, C4.1, C6.1, JP2.1, JP3.2, JP5.2, JP6.2, K1.3 (3V3), K2.3 (3V3), R6.2, R7.2, U1.2 (G2), U1.5 (G1), U2.5 (VOUT), U3.6 (VBAT), U3.9 (VDD), U3.11 (BS1)
CS: R6.1, U3.13 (CSn)
GND: C1.1, C2.1, C3.2, C4.2, C6.2, C7.2, C9.2, D1.2 (K), K1.4 (GND), K1.5 (SHIELD), K2.4 (GND), K2.5 (SHIELD), K3.1, R8.1, R9.2, U2.2 (GND), U3.1 (N.C.(GND)), U3.8 (VSS), U3.10 (BS0), U3.12 (BS2), U3.29 (VLSS), U3.30 (N.C.(GND))
unnamed: C1.2, JP4.1, U2.1 (VIN), U2.3 (EN)
unnamed: C5.1, U3.5 (C1N)
unnamed: C5.2, U3.4 (C1P)
unnamed: C7.1, U3.27 (VCOMH)
unnamed: C8.1, U3.3 (C2N)
unnamed: C8.2, U3.2 (C2P)
unnamed: C9.1, U3.28 (VCC)
unnamed: D1.1 (A), R5.2
unnamed: JP2.2, R5.1
unnamed: R9.1, U3.26 (IREF)
unnamed: JP6.1, R8.2, U3.15 (D/Cn)
RST: R7.1, U3.14 (RESn)
SCL3,3: K1.1 (SCL), K2.1 (SCL), R4.1, U1.4 (S1), U3.18 (D0)
SCL5: K3.4, R2.2, U1.3 (D1)
SCL_PULL3,3: JP3.1, R4.2
SCL_PULL5: JP1.1, R2.1
SDA3,3: K1.2 (SDA), K2.2 (SDA), R1.2, U1.1 (S2), U3.19 (D1), U3.20 (D2)
SDA5: K3.3, R3.1, U1.6 (D2)
SDA_PULL3,3: JP3.3, R1.1
SDA_PULL5: JP1.3, R3.2
VCC: JP1.2, JP4.2, JP5.1, K3.2

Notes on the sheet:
I2C HEADER & easyC CONNECTOR
VOLTAGE LEVEL TRANSLATOR
PWR LED
PULL-UP RESISTOR
3V3 VOLTAGE REGULATOR
0.96" OLED
I2C ADDRESS JUMPER
